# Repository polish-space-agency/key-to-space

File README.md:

<p align="right">
  <b>Polski</b> | <a href="README.en.md">English</a>
</p>

# Klucz do Kosmosu

```
OŚWIADCZENIE LICENCYJNE PROJEKTU

PL: Cała zawartość tego repozytorium, w tym pliki projektowe programu KiCad (schematy i projekty płytek PCB) oraz dokumentacja techniczna, udostępniana jest na licencji:
Creative Commons Uznanie autorstwa - Użycie niekomercyjne - Na tych samych warunkach 4.0 Międzynarodowe (CC BY-NC-SA 4.0).

Pełna treść licencji dostępna jest pod adresem: https://creativecommons.org/licenses/by-nc-sa/4.0/legalcode.txt

WARUNKI SZCZEGÓŁOWE I INTENCJA AUTORA:
1. UŻYTEK NIEKOMERCYJNY: Zezwala się na kopiowanie, modyfikowanie oraz wytwarzanie fizycznych egzemplarzy urządzenia wyłącznie do celów niekomercyjnych, prywatnych, hobbystycznych (np. przez krótkofalowców, majsterkowiczów) oraz statutowych (przez organizacje pozarządowe / NGO).
2. SPECJALNE ZEZWOLENIE DLA PLACÓWEK OŚWIATOWYCH: Oficjalne szkoły, uczelnie wyższe oraz inne placówki dydaktyczne są wyraźnie uprawnione do wytwarzania oraz zlecania produkcji tego urządzenia (w tym zamawiania partii płytek PCB w zewnętrznych przedsiębiorstwach) na własne, wewnętrzne potrzeby edukacyjne i szkoleniowe.
3. OZNACZENIE AUTORA NA PCB (WARUNEK "BY"): Zgodnie z warunkiem Uznania Autorstwa, zabrania się usuwania, modyfikowania lub zakrywania oznaczeń autora (nazwiska, nicku lub logo) umieszczonych na warstwie opisowej (silkscreen) płytki PCB. Każda wyprodukowana płytka musi te oznaczenia zachować w oryginalnej formie.
```

**Dokumentacja techniczna – edukacyjne urządzenie elektroniczne, wersja szkolna**

Projekt powstał na zlecenie Polskiej Agencji Kosmicznej na potrzeby działań edukacyjnych dla misji IGNIS. Realizatorami misji IGNIS byli: Ministerstwo Rozwoju i Technologii, Polska Agencja Kosmiczna i Europejska Agencja Kosmiczna.
Projekt wyprodukowano i rozdano w liczbie 100 000 egzemplarzy, nieodpłatnie do polskich szkół.

Na prośby kierowane do POLSA, projekt udostępniony jest dla hobbystów i wszystkich zainteresowanych niekomercyjnym jego użyciem.

## Spis treści

- [Słownik skrótów](#słownik-skrótów)
- [1. Wprowadzenie](#1-wprowadzenie)
- [2. Specyfikacja techniczna](#2-specyfikacja-techniczna)
- [3. Opis urządzenia](#3-opis-urządzenia)
- [4. Lista komponentów (BOM)](#4-lista-komponentów-bom)
- [5. Testy](#5-testy)
- [6. Informacje dotyczące produkcji](#6-informacje-dotyczące-produkcji)

## Słownik skrótów

| Skrót | Rozwinięcie |
|-------|-------------|
| BOM   | Bill of Materials |
| FR    | Flame Retardant |
| HAL   | Hot Air Leveling |
| ISS   | International Space Station |
| LED   | Light-Emitting Diode |
| PCB   | Printed Circuit Board |
| STEM  | Science, Technology, Engineering, Mathematics |
| THT   | Through-Hole Technology |
| USB   | Universal Serial Bus |

## 1. Wprowadzenie

Niniejsza dokumentacja techniczna zawiera kluczowe informacje na temat projektu edukacyjnego urządzenia elektronicznego *Klucz do kosmosu*, zaprojektowanego dla Polskiej Agencji Kosmicznej. Urządzenie (płytka PCB z zestawem komponentów do samodzielnego montażu) jest częścią większego programu edukacyjnego promującego naukę STEM i będzie wykorzystywane do nauczania podstaw elektroniki i lutowania w szkołach.

Dokumentacja zawiera specyfikację techniczną, opis budowy i działania, a także informacje przydatne przy ewentualnej produkcji tego urządzenia.

## 2. Specyfikacja techniczna

### 2.1. Wymiary

Płytka PCB w kształcie satelity. Grubość laminatu typowa – 1,57 mm (0,063 cala). Płytka posiada sześć otworów montażowych o średnicy 3,2 mm.

*Rysunek 1: Wymiary płytki PCB*

### 2.2. Montaż

Urządzenie jest przeznaczone do samodzielnego montażu, dlatego zastosowano w nim łatwe do lutowania elementy przewlekane (THT).

*Rysunek 2: Płytka z wlutowanymi elementami*

Całkowita masa urządzenia (PCB z komponentami): około 40 g.

### 2.3. Zasilanie

Układ może być zasilany napięciem stałym z zakresu od 3 V do 9 V. Daje to szeroki wybór źródła zasilania – np. USB (zasilacz, ładowarka, laptop, power bank) lub popularne baterie (1,5 V typu AA lub AAA).

Maksymalny pobór prądu: poniżej 200 mA.

## 3. Opis urządzenia

Urządzenie składa się z dwóch niezależnych analogowych układów elektronicznych realizujących następujące funkcje:

- **klucz telegraficzny** – układ emitujący dźwięk po naciśnięciu przycisku,
- **klaskacz** – układ reagujący na dźwięk świeceniem diod LED.

Projekt wykorzystuje zróżnicowany zestaw elementów elektronicznych, takich jak rezystory, kondensatory, tranzystory, układy scalone, diody LED, przetworniki dźwięku, a także elementy mechaniczne. Ten zróżnicowany zestaw komponentów stanowi cenne narzędzie edukacyjne dla użytkowników, którzy mogą dowiedzieć się o zastosowaniach różnych komponentów, zrozumieć ich działanie i zależności między nimi.

### 3.1. Budowa

#### 3.1.1. Płytka PCB

Zaprojektowana płytka PCB jest dwustronna (dwuwarstwowa), pokryta niebieską maską lutowniczą z opisami od strony elementów. Boczne skrzydła, przypominające panele słoneczne satelity, nie są częścią układu elektronicznego – stanowią jedynie ozdobę i miejsce na logo.

*Rysunek 3: Płytka PCB – strona elementów*

*Rysunek 4: Płytka PCB – strona lutowania*

#### 3.1.2. Rozmieszczenie komponentów

Poniższy rysunek przedstawia wizualizację płytki drukowanej z rozmieszczonymi komponentami i podziałem na układy elektroniczne realizujące określone funkcje.

*Rysunek 5: Rozmieszczenie komponentów na płytce PCB*

### 3.2. Klucz telegraficzny

Obwód elektroniczny realizujący funkcję klucza telegraficznego składa się z następujących elementów:

- mikroprzełącznik,
- generator astabilny,
- brzęczyk piezoelektryczny.

Po naciśnięciu mikroprzełącznika monostabilnego (S1) włączane jest zasilanie obwodu generatora astabilnego, który generuje zmienny sygnał dla brzęczyka piezoelektrycznego (BZ1). Brzęczyk przetwarza zmienne napięcie elektryczne w sygnał akustyczny.

*Rysunek 6: Schemat układu klucza telegraficznego*

Generator astabilny zbudowany na układzie timera NE555P (U1) to proste, ale wszechstronne rozwiązanie służące do generowania sygnałów prostokątnych o zmiennej częstotliwości i współczynniku wypełnienia. Jego elastyczność, niezawodność i łatwość implementacji czynią go popularnym rozwiązaniem w wielu aplikacjach elektronicznych.

Podczas działania układu kondensator C4 jest cyklicznie ładowany i rozładowywany. Układ NE555P kontroluje ten proces i zmienia stan logiczny na wyjściu Q, generując okresowy przebieg prostokątny.

Kondensator C3 służy do blokowania szybkich zmian napięć odniesienia podawanych na układ U1 z dzielnika.

Częstotliwość generowanego przebiegu można wyznaczyć zgodnie z zależnością:

$$f = \frac{1{,}44}{(R_4 + 2R_5)\,C_4}$$

Współczynnik wypełnienia generowanego przebiegu:

$$D = \frac{R_4 + R_5}{R_4 + 2R_5}$$

Wartości rezystancji R4 i R5 oraz pojemność kondensatora C4 mają bezpośredni wpływ na częstotliwość i cykl pracy generowanego przebiegu:

- zwiększenie C4 zwiększy czas cyklu, a tym samym zmniejszy częstotliwość,
- zwiększenie R4 zwiększy czas trwania stanu wysokiego (*Time High*), ale nie wpłynie na czas trwania stanu niskiego (*Time Low*),
- zwiększenie R5 zwiększy czas trwania stanu wysokiego (*Time High*), zwiększy czas trwania stanu niskiego (*Time Low*) i zmniejszy cykl pracy (do minimum 50%).

Generowany sygnał podawany na brzęczyk można obserwować, podłączając oscyloskop do punktów pomiarowych TP1 i TP2 (masa) na płytce drukowanej.

Poniższy rysunek przedstawia obliczenia wykonane dla wartości elementów użytych w obwodzie.

*Rysunek 7: Wyliczone parametry przebiegu dla R4 = 10 kΩ, R5 = 2,2 kΩ i C4 = 100 nF*

Parametry rzeczywistego przebiegu mogą się różnić od wyliczonych ze względu na tolerancję wartości komponentów zastosowanych do budowy układu.

*Rysunek 8: Rzeczywisty przebieg obserwowany na oscyloskopie*

Zmiana rezystancji R4 na 15 kΩ spowoduje zmniejszenie częstotliwości generowanego przebiegu.

*Rysunek 9: Zmiana parametrów po zwiększeniu rezystancji R4*

*Rysunek 10: Przebieg po zwiększeniu rezystancji R4*

Zamiana miejscami rezystancji R4 i R5 oraz zmniejszenie pojemności C4 do 22 nF powoduje zwiększenie częstotliwości generowanego przebiegu i zmniejszenie współczynnika wypełnienia. Może to poprawić brzmienie brzęczyka.

*Rysunek 11: Zwiększenie częstotliwości generowanego przebiegu*

*Rysunek 12: Rzeczywisty przebieg po zwiększeniu częstotliwości*

Zamiast brzęczyka piezoelektrycznego można zastosować brzęczyk elektromagnetyczny (również bez wbudowanego generatora). Na płytce są otwory dostosowane do mniejszego rastra wyprowadzeń i średnicy tego typu komponentu.

### 3.3. Klaskacz

W układzie realizującym funkcjonalność klaskacza można wyróżnić:

- mikrofon z układem przedwzmacniacza,
- wzmacniacz sygnału,
- wskaźnik zbudowany z diod LED.

Mikrofon reaguje na zmiany ciśnienia akustycznego w otoczeniu, generując zmienne napięcie wyjściowe proporcjonalne do natężenia dźwięku. Sygnał ten jest wzmacniany i wykorzystany do wysterowania diod LED.

*Rysunek 13: Schemat układu „klaskacza”*

Zastosowany mikrofon elektretowy (MK1) charakteryzuje się niewielkimi rozmiarami, niską impedancją wyjściową i szerokim zakresem częstotliwości. Ten typ mikrofonu posiada wbudowany przedwzmacniacz w postaci tranzystora polowego. Tranzystor ten musi być zasilany z zewnętrznego źródła napięcia poprzez rezystor polaryzujący R1, który pełni również rolę obciążenia. Wartość tego rezystora jest dobierana tak, żeby zapewnić odpowiednie napięcie pracy mikrofonu, i ma również wpływ na wzmocnienie. Kondensator C2 na wyjściu służy do eliminacji składowej stałej.

Tranzystory Q1 i Q2 służą do wzmacniania sygnału z mikrofonu i sterowania diodami LED. Zmiany sygnału mikrofonu powodują zmiany prądu kolektora tranzystora Q2, zmieniając w ten sposób intensywność diod LED. Rezystor R3 może być używany do regulacji jasności diod LED.

## 4. Lista komponentów (BOM)

### 4.1. Elementy montowane na płytce PCB

Wszystkie elementy do montażu przewlekanego (THT).

| Element | Wartość/typ | Opis | Obudowa | Symbol – przykład |
|---------|-------------|------|---------|-------------------------------|
| R1 | 4.7kΩ[^1] | Rezystor węglowy, 0.25W, ±5% | Osiowa, Ø2.3x6mm | CF1/4W-4K7 |
| R2 | 1MΩ | Rezystor węglowy, 0.25W, ±5% | Osiowa, Ø2.3x6mm | CF1/4W-1M |
| R3 | 10kΩ[^2] | Rezystor węglowy, 0.25W, ±5% | Osiowa, Ø2.3x6mm | CF1/4W-10K |
| R4 | 10kΩ[^3] | Rezystor węglowy, 0.25W, ±5% | Osiowa, Ø2.3x6mm | CF1/4W-10K |
| R5 | 2.2kΩ | Rezystor węglowy, 0.25W, ±5% | Osiowa, Ø2.3x6mm | CF1/4W-2K2 |
| C3 | 10nF | Kondensator ceramiczny, 50V | 2.54mm | CC-10N |
| C4 | 100nF[^4] | Kondensator ceramiczny, 50V | 2.54mm | CC-100N |
| C1 | 100µF | Kondensator elektrolityczny, 25V | Ø6x11mm, 2.5mm | EWH1EV101E11OT |
| C2 | 1µF | Kondensator elektrolityczny, 50V | Ø5x11mm, 2.5mm | EWH1HM010D11X25T |
| C5 | 10µF | Kondensator elektrolityczny, 50V | Ø5x11mm, 2.5mm | EWH1HM100D11X25T |
| U1 | NE555P | Układ scalony, timer | DIP8 | NE555P |
| Q1, Q2 | BC547B[^5] | Tranzystor bipolarny NPN | TO92 | BC547B |
| D1..D5 | | Dioda LED, dyfuzyjna, niebieska, jasność do 1000mcd | 5mm, czoło wypukłe | L-7113QBDL-D |
| MK1[^6] | | Mikrofon elektretowy, 1..10V, 0.5mA, -44dB (min.) | Ø9.7mm, 2.5mm | LD-MC-9765P |
| BZ1 | | Brzęczyk piezoelektryczny bez generatora, 1..10V, 1mA | Ø13.8x6.8mm, 7.6mm | AT-1438-TWT-R |
| S1 | | Mikroprzełącznik monostabilny | 12x12x4.3mm | TACT-24N |
| J1 | | Złącze śrubowe, kątowe 90º, dwutorowe | 5.08mm | 282837-2 lub TB-5.08-P-2P/BL |

Dodatkowe elementy dołączane do zestawu (do eksperymentów, niemontowane na stałe):

| Element | Zamiennik dla | Liczba sztuk |
|---------|:-------------:|:------------:|
| Rezystor 4.7kΩ | R3 | 1 |
| Rezystor 15kΩ | R3, R4, R5 | 2 |
| Rezystor 30kΩ | R3 | 1 |
| Kondensator ceramiczny 22nF | C4 | 1 |

[^1]: Alternatywnie 10kΩ w zależności od czułości zastosowanego mikrofonu – zwiększenie rezystancji może poprawić działanie układu klaskacza.
[^2]: Zmiana rezystancji R3 w zależności od napięcia zasilania układu powoduje zmianę intensywności świecenia diod LED – przy wyższym napięciu zasilania zwiększenie rezystancji zmniejszy intensywność świecenia diod LED i może w niektórych przypadkach poprawić brzmienie brzęczyka (proponowane dodatkowe rezystory 4.7kΩ, 15kΩ i 30kΩ).
[^3]: Do zestawu powinny być dodane inne wartości rezystorów R4 i R5, aby umożliwić eksperymenty związane ze zmianą parametrów generowanego przebiegu (proponowany dodatkowy rezystor 15kΩ).
[^4]: Podobnie jak rezystory R4 i R5, pojemność C4 ma również bezpośredni wpływ na parametry generowanego przebiegu, więc do zestawu powinna być dodana również inna wartość pojemności (np. 22nF).
[^5]: Układ został przetestowany również z innymi typami tranzystorów NPN (BC183, BC546, BC548, BC549, BC550).
[^6]: Najlepiej sprawdził się mikrofon OEM, dla którego nie udało się ustalić symbolu i nazwy producenta, a także uzyskać karty katalogowej – w tabeli podany został komponent alternatywny zastosowany w wersji dla ISS. Mikrofon OEM jest dostępny pod kodem UCC-00740.

### 4.2. Komponenty dodatkowe

Proponowane elementy dodatkowe związane z wyborem źródła zasilania:

- koszyk na 2 lub 3 baterie (typu AA lub AAA) z przewodami – w zestawie 1 szt. (koszyk na 2 baterie AAA),
- wtyk USB typ A na przewód do lutowania – 1 szt.

Koszyk na baterie lub przygotowany kabel z wtyczką USB należy podłączyć do złącza zaciskowego śrubowego na płytce PCB (oznaczonego symbolem J1) z zachowaniem odpowiedniej polaryzacji.

|  |  |
|:---:|:---:|
| *Rysunek 14: Koszyk na baterie 2xAAA* | *Rysunek 15: Wtyczka USB z obudową* |

Opcjonalne elementy montażowe:

- kołki dystansowe poliamidowe (M3, 10mm) – 6 szt.,
- śruby nylonowe (M3, 6mm) – 6 szt.

## 5. Testy

### 5.1. Pobór prądu

Urządzenie charakteryzuje się niskim zużyciem energii. Testy z wykorzystaniem modułu analizy parametrów zasilania (*Power Profiler Kit*) jako źródła zasilania wykazały, że podczas normalnej pracy przy napięciu zasilania 5 V szczytowe wartości prądu nie przekraczają 150 mA.

*Rysunek 16: Pobór prądu podczas pracy urządzenia przy napięciu zasilania 5 V*

*Rysunek 17: Pobór prądu podczas używania klucza telegraficznego*

*Rysunek 18: Prąd rozruchowy w chwili uruchomienia urządzenia*

## 6. Informacje dotyczące produkcji

### 6.1. Płytka PCB – specyfikacja techniczna

| Parametr | Wartość |
|----------|---------|
| Rodzaj laminatu | FR-4 |
| Wymiary zewnętrzne płytki | 153x82mm (1.26dm²) |
| Grubość laminatu bazowego | 1.55mm |
| Liczba warstw | 2 |
| Grubość miedzi | 35µm (1oz) |
| Liczba otworów na płytce | 58 + 6 montażowych |
| Metalizacja otworów | Tak |
| Maska lutownicza (soldermaska) | Dwustronna w kolorze niebieskim |
| Cynowanie | HAL |
| Nietypowy kształt płytki | Tak |
| Frezowanie płytki i otworów | Tak |
| Opis (silkscreen) | Jednostronny w kolorze białym |

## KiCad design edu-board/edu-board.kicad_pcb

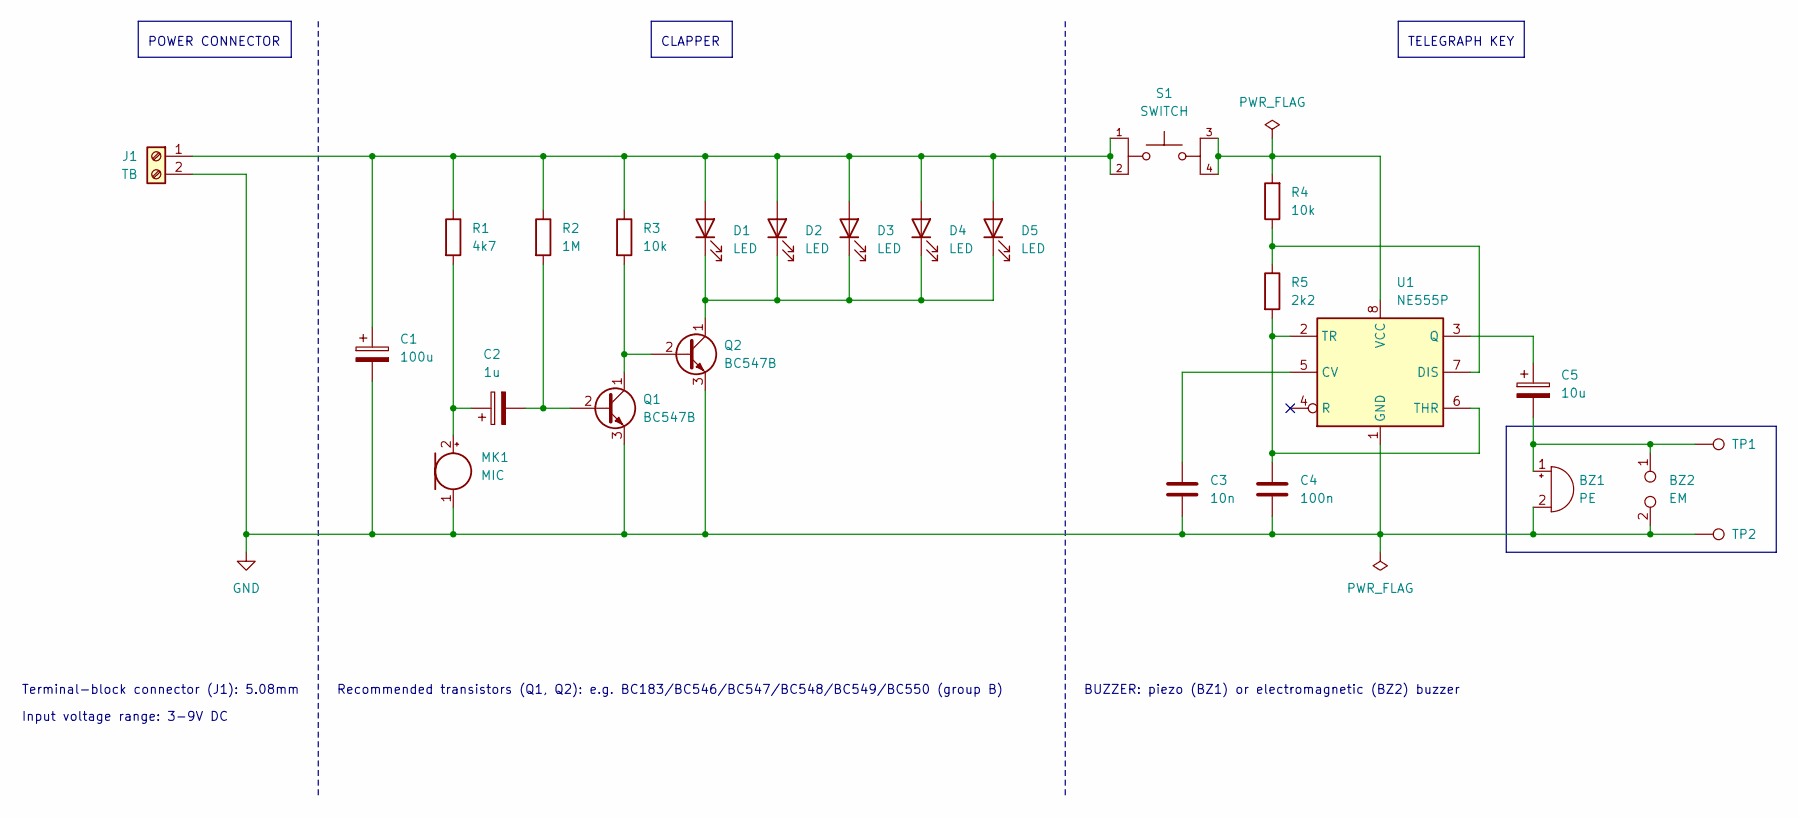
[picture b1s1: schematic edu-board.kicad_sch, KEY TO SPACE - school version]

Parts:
BZ1: PE; Buzzer_15x7.5RM7.6
BZ2: EM; MagneticBuzzer_ProSignal_ABT-410-RC
C1: 100u; CP_Radial_D6.3mm_P2.50mm
C2: 1u; CP_Radial_D5.0mm_P2.50mm
C3: 10n; C_Disc_D3.8mm_W2.6mm_P2.50mm
C4: 100n; C_Disc_D5.0mm_W2.5mm_P2.50mm
C5: 10u; CP_Radial_D5.0mm_P2.50mm
D1, D2, D3, D4, D5: LED; LED_D5.0mm
J1: TB; TE_282837-2
MK1: MIC; CUI_CMA-6542PF
Q1, Q2: BC547B; TO-92_HandSolder
R1: 4k7; R_Axial_DIN0207_L6.3mm_D2.5mm_P10.16mm_Horizontal
R2: 1M; R_Axial_DIN0207_L6.3mm_D2.5mm_P10.16mm_Horizontal
R3, R4: 10k; R_Axial_DIN0207_L6.3mm_D2.5mm_P10.16mm_Horizontal
R5: 2k2; R_Axial_DIN0207_L6.3mm_D2.5mm_P10.16mm_Horizontal
S1: SWITCH; SW_TL1100F160Q; PARTREV D
TP1, TP2: TestPoint; PinHeader_1x01_P2.54mm_Vertical
U1: NE555P; DIP-8_W7.62mm

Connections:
GND: BZ1.2 (+), BZ2.2, C1.2, C3.2, C4.2, J1.2, MK1.1 (-), Q1.3 (E), Q2.3 (E), TP2.1, U1.1 (GND)
unnamed: R4.2, S1.3, S1.4, U1.8 (VCC)
unnamed: BZ1.1 (-), BZ2.1, C5.2, TP1.1
unnamed: C1.1, D1.2 (A), D2.2 (A), D3.2 (A), D4.2 (A), D5.2 (A), J1.1, R1.1, R2.1, R3.1, S1.1, S1.2
unnamed: D1.1 (K), D2.1 (K), D3.1 (K), D4.1 (K), D5.1 (K), Q2.1 (C)
unnamed: C2.1, MK1.2 (+), R1.2
unnamed: C2.2, Q1.2 (B), R2.2
unnamed: Q1.1 (C), Q2.2 (B), R3.2
unnamed: C3.1, U1.5 (CV)
unnamed: R4.1, R5.1, U1.7 (DIS)
unnamed: C5.1, U1.3 (Q)
unnamed: C4.1, R5.2, U1.2 (TR), U1.6 (THR)

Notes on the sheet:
POWER CONNECTOR
BUZZER: piezo (BZ1) or electromagnetic (BZ2) buzzer
Input voltage range: 3-9V DC
Terminal-block connector (J1): 5.08mm
Recommended transistors (Q1, Q2): e.g. BC183/BC546/BC547/BC548/BC549/BC550 (group B)
TELEGRAPH KEY
CLAPPER

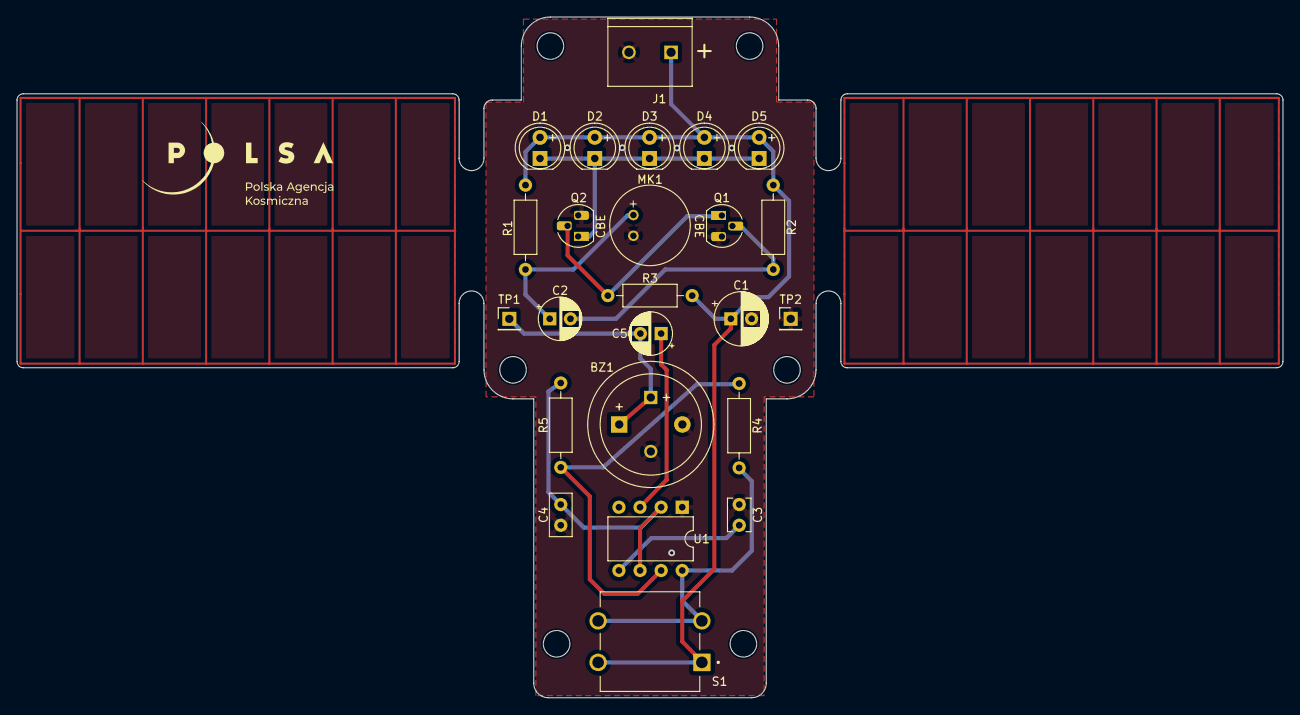
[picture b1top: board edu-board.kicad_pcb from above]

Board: 2 copper layers, 152.5 x 82.0 mm, 25 parts (0 on the bottom side), 12 nets.
